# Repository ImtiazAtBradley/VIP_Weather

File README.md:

# This Repository Has Moved!!!!!

[github.com/ece398-buvip/vip-weather](https://github.com/ece398-buvip/vip-weather)

# Bradley Weather Station - Overview

The source code for the Bradley Weather Station website/api/firmware/broker. The data produced by the station is available at [weather.jacobsimeone.net](https://weather.jacobsimeone.net). 

- [Hardware Design on OnShape](https://cad.onshape.com/documents/38c15368c41f2224b0adceca/w/e0d05cb6b75a73d47582f798/e/6f88f03cdb676fd77e352c81)
- [Documentation](https://litemage.github.io/vip-weather-docs/)
- [Documentation GitHub (separate from this repository)](https://github.com/Litemage/vip-weather-docs)

# Contributors

**Spring 2024**
- Jacob S. 
- Kyle K.
- Christopher H.
- Emily A.
- Owen J.
- Samantha P.
- Dr. Imtiaz - **Advisor**

**Fall 2024**
- Ryuto N.
- Freddie M.
- Logan V.
- Grace T.

**Spring 2025**
- Matthew V.
- Riley P.

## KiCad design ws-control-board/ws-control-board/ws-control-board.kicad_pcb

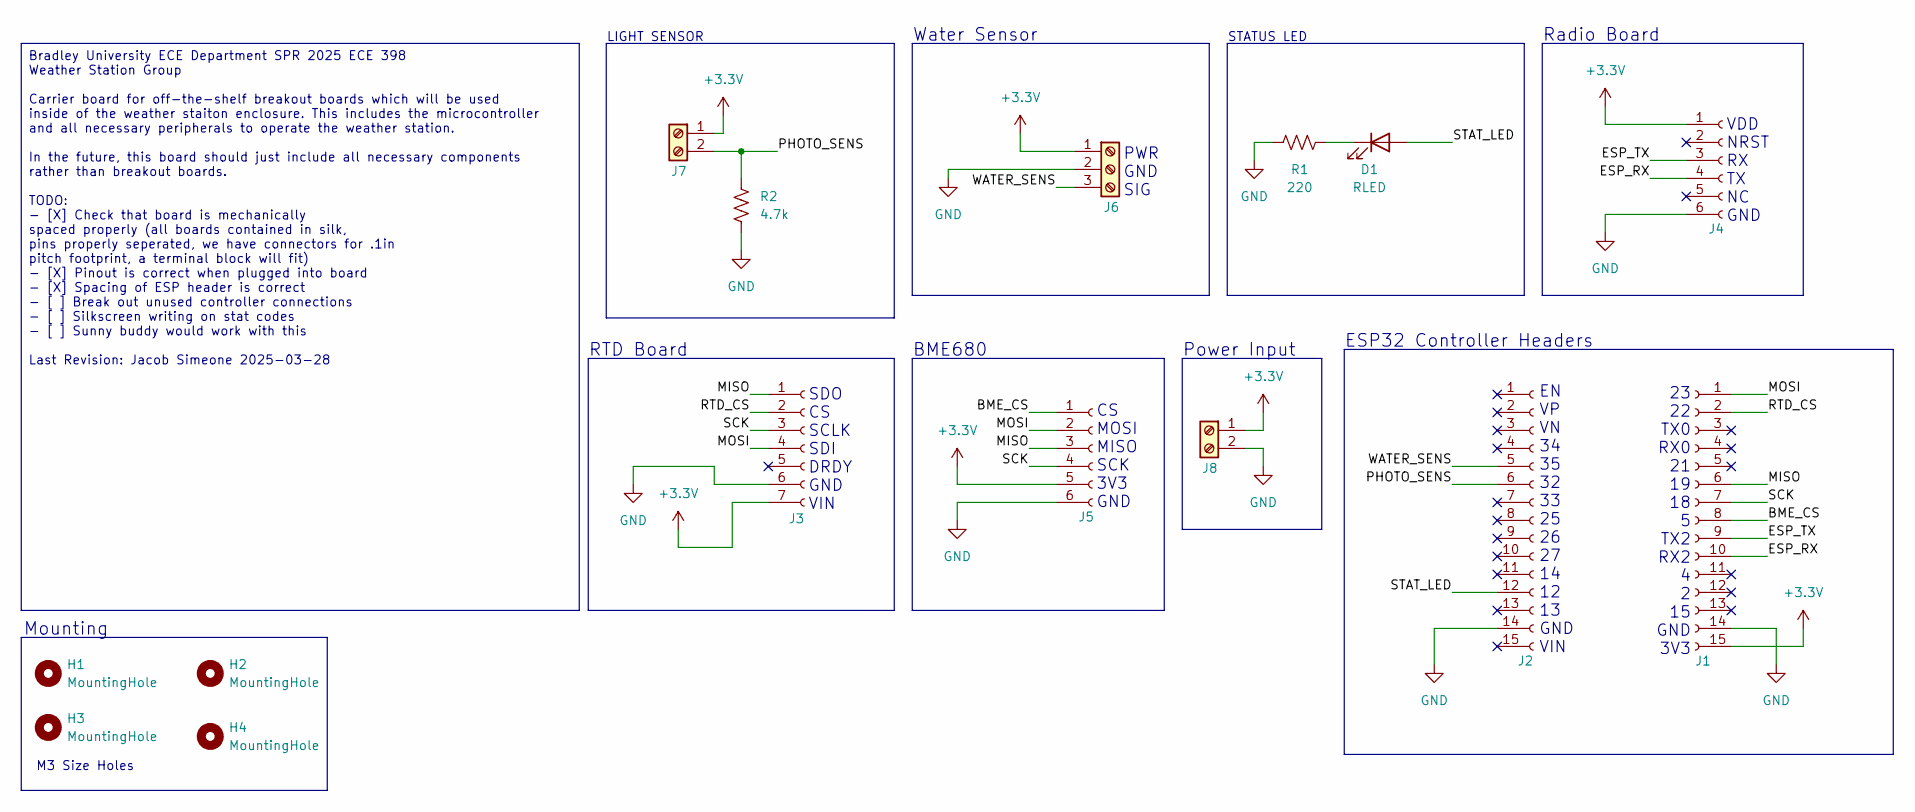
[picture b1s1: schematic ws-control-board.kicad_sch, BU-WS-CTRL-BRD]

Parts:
D1: RLED; LED_D5.0mm
H1, H2, H3, H4: MountingHole; MountingHole_3.2mm_M3
J1, J2: Conn_01x15_Socket; PinSocket_1x15_P2.54mm_Vertical
J3: Conn_01x07_Socket; PinSocket_1x07_P2.54mm_Vertical
J4, J5: Conn_01x06_Socket; PinSocket_1x06_P2.54mm_Vertical
J6: Screw_Terminal_01x03; PinHeader_1x03_P2.54mm_Vertical
J7, J8: Screw_Terminal_01x02; PinHeader_1x02_P2.54mm_Vertical
R1: 220; R_Axial_DIN0207_L6.3mm_D2.5mm_P10.16mm_Horizontal
R2: 4.7k; R_Axial_DIN0207_L6.3mm_D2.5mm_P10.16mm_Horizontal

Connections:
+3.3V: J1.15, J3.7, J4.1, J5.5, J6.1, J7.1, J8.1
/BME_CS: J1.8, J5.1
/ESP_RX: J1.10, J4.4
/ESP_TX: J1.9, J4.3
/MISO: J1.6, J3.1, J5.3
/MOSI: J1.1, J3.4, J5.2
/PHOTO_SENS: J2.6, J7.2, R2.2
/RTD_CS: J1.2, J3.2
/SCK: J1.7, J3.3, J5.4
/STAT_LED: D1.2 (A), J2.12
/WATER_SENS: J2.5, J6.3
GND: J1.14, J2.14, J3.6, J4.6, J5.6, J6.2, J8.2, R1.1, R2.1
unnamed: D1.1 (K), R1.2

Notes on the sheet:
Radio Board
CS MOSI MISO SCK 3V3 GND
PWR GND SIG
SDO CS SCLK SDI DRDY GND VIN
M3 Size Holes
RTD Board
Mounting
STATUS LED
VDD NRST RX TX NC GND
23 22 TX0 RX0 21 19 18 5 TX2 RX2 4 2 15 GND 3V3
BME680
EN VP VN 34 35 32 33 25 26 27 14 12 13 GND VIN
LIGHT SENSOR
Power Input
ESP32 Controller Headers
Water Sensor
Bradley University ECE Department SPR 2025 ECE 398 Weather Station Group Carrier board for off-the-shelf breakout boards which will be used inside of the weather staiton enclosure. This includes the microcontroller and all necessary peripherals to operate the weather station. In the future, this bo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

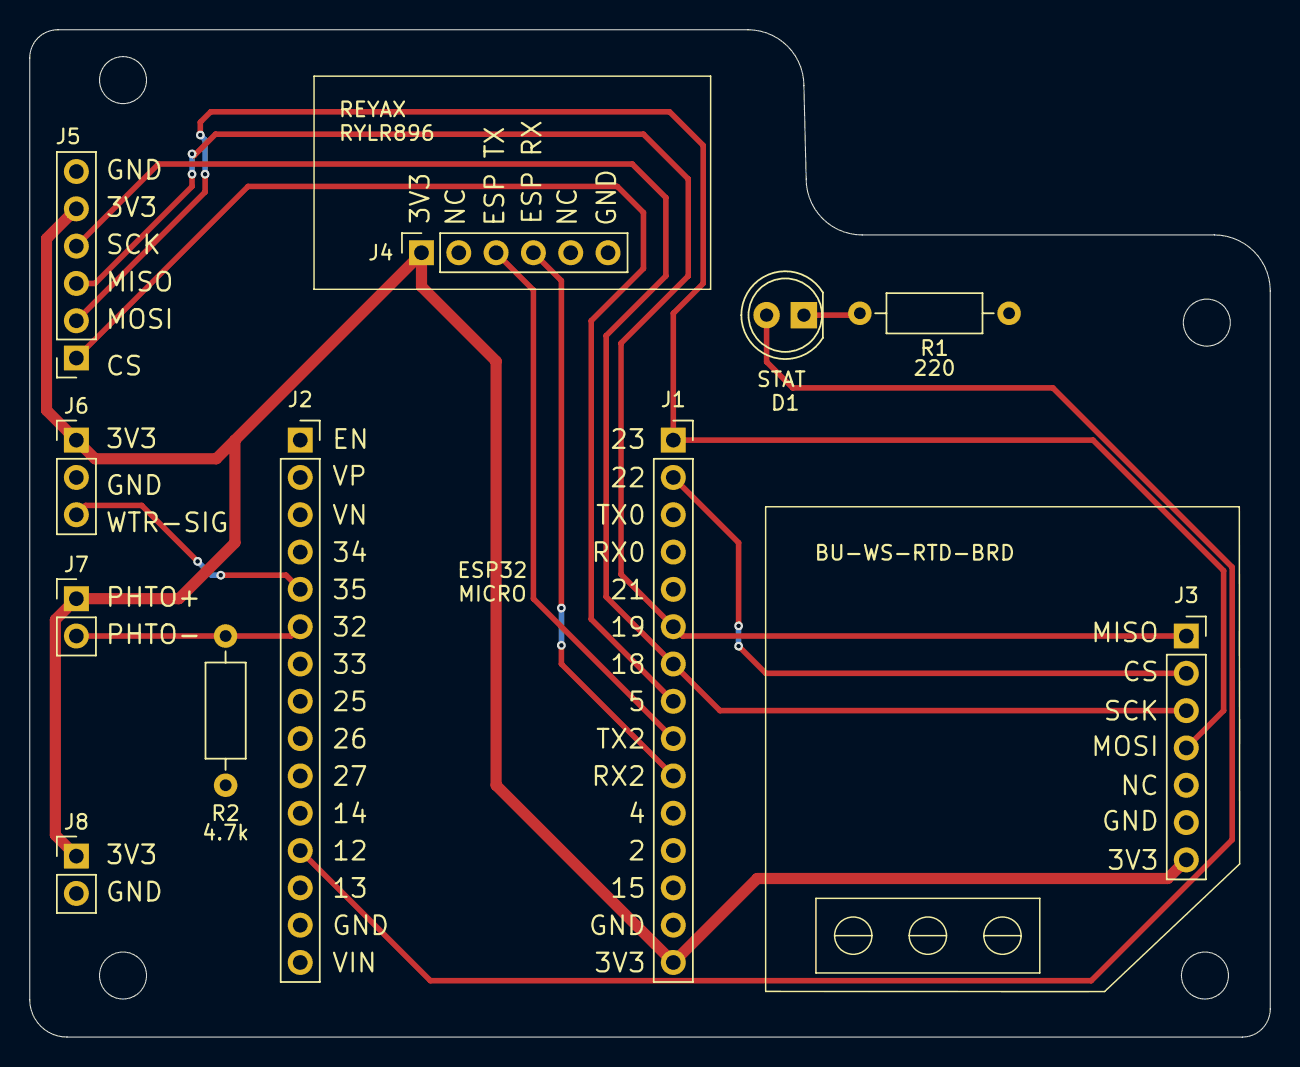
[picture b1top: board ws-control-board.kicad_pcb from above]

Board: 2 copper layers, 84.5 x 68.6 mm, 15 parts (0 on the bottom side), 13 nets.

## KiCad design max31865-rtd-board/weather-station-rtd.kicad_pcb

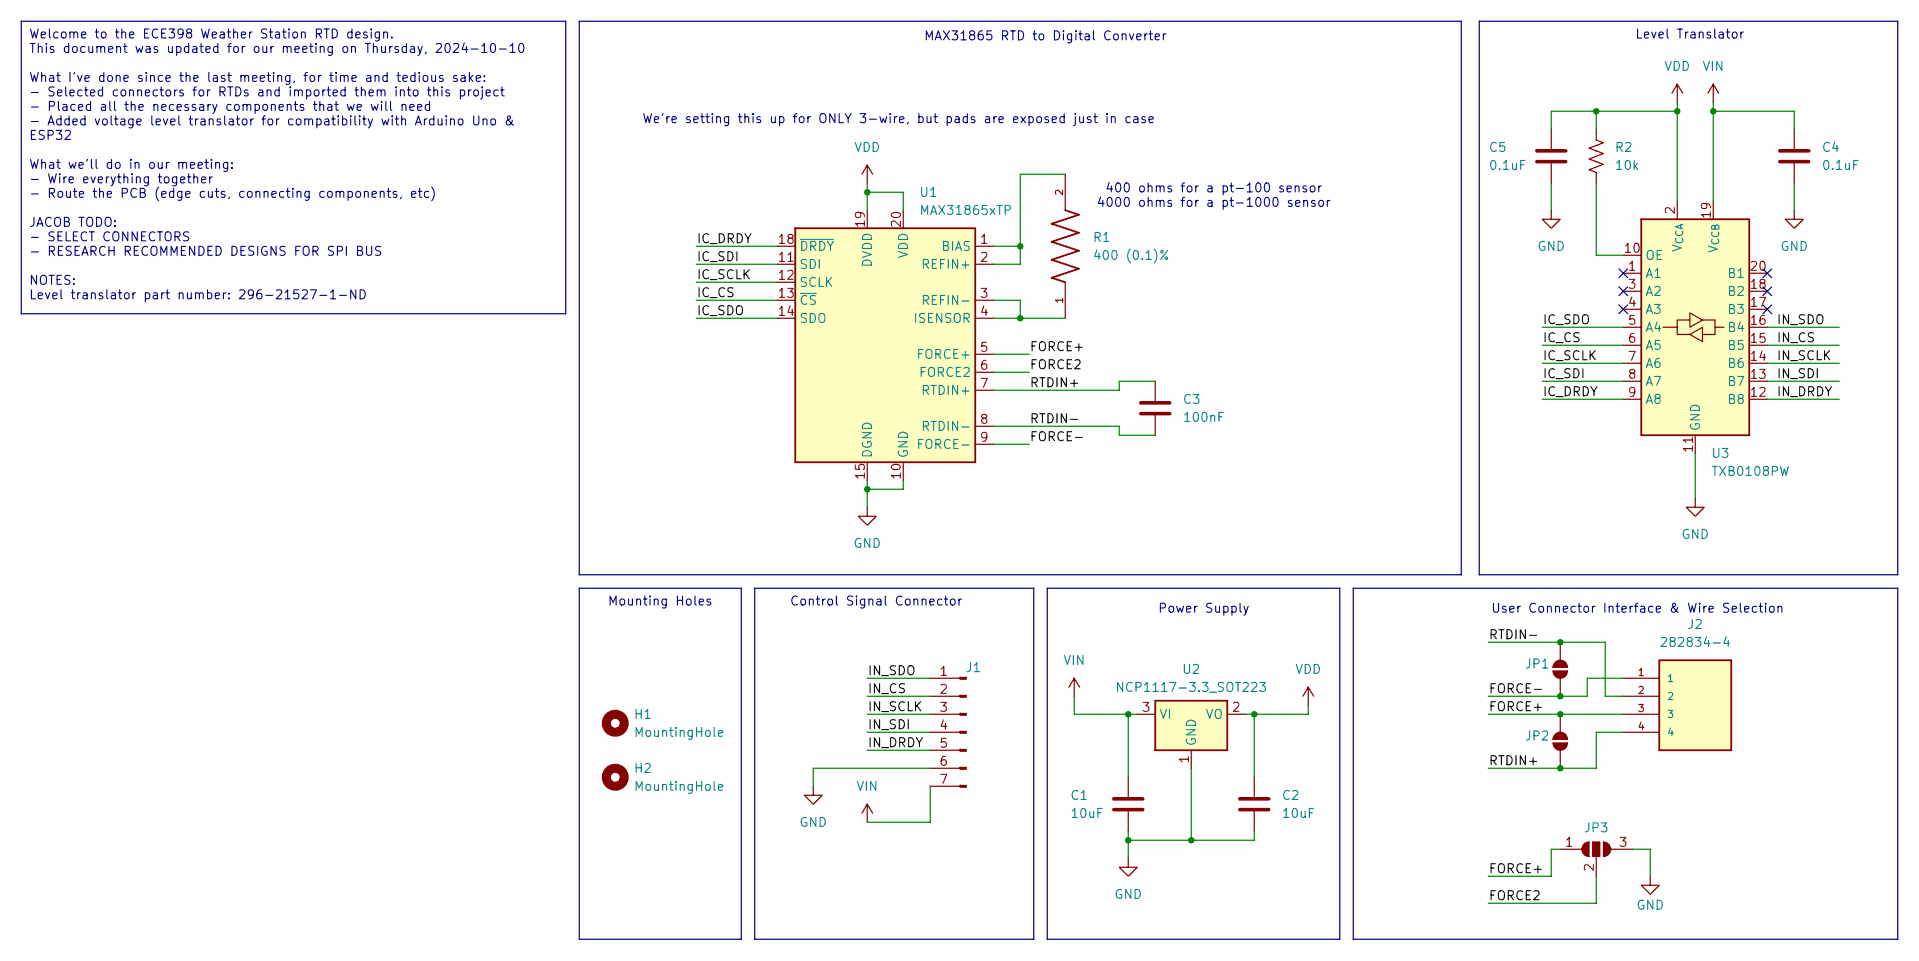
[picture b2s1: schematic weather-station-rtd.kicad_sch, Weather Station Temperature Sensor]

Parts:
C1, C2: 10uF; C_0805_2012Metric
C3: 100nF; C_0805_2012Metric
C4, C5: 0.1uF; C_0805_2012Metric
H1, H2: MountingHole; MountingHole_3.2mm_M3
J1: Conn_01x05_Pin; PinHeader_1x07_P2.54mm_Vertical
J2: 282834-4; TE_282834-4; PARTREV D
JP1, JP2: SolderJumper-2_P1.3mm_Open_TrianglePad1.0x1.5mm
JP3: SolderJumper-3_P1.3mm_Open_RoundedPad1.0x1.5mm_NumberLabels
R1: 400 (0.1)%; RESC3116X65N
R2: 10k; C_0805_2012Metric
U1: MAX31865xTP; TQFN-20-1EP_5x5mm_P0.65mm_EP3.25x3.25mm
U2: NCP1117-3.3_SOT223; SOT-223-3_TabPin2
U3: TXB0108PW; TSSOP-20_4.4x6.5mm_P0.65mm

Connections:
/FORCE2: JP3.2 (C), U1.6 (FORCE2)
/FORCE+: J2.3, JP2.2 (B), JP3.1 (A), U1.5 (FORCE+)
/FORCE-: J2.1, JP1.1 (A), U1.9 (FORCE-)
/IC_CS: U1.13 (~CS), U3.6 (A5)
/IC_DRDY: U1.18 (~DRDY), U3.9 (A8)
/IC_SCLK: U1.12 (SCLK), U3.7 (A6)
/IC_SDI: U1.11 (SDI), U3.8 (A7)
/IC_SDO: U1.14 (SDO), U3.5 (A4)
/IN_CS: J1.2, U3.15 (B5)
/IN_DRDY: J1.5, U3.12 (B8)
/IN_SCLK: J1.3, U3.14 (B6)
/IN_SDI: J1.4, U3.13 (B7)
/IN_SDO: J1.1, U3.16 (B4)
/RTDIN+: C3.1, J2.4, JP2.1 (A), U1.7 (RTDIN+)
/RTDIN-: C3.2, J2.2, JP1.2 (B), U1.8 (RTDIN-)
GND: C1.2, C2.2, C4.2, C5.2, J1.6, JP3.3 (B), U1.10 (GND), U1.15 (DGND), U1.16 (GND), U1.21 (GND), U2.1 (GND), U3.11 (GND)
unnamed: R1.2, U1.1 (BIAS), U1.2 (REFIN+)
unnamed: R1.1, U1.3 (REFIN-), U1.4 (ISENSOR)
unnamed: R2.2, U3.10 (OE)
VDD: C2.1, C5.1, R2.1, U1.19 (DVDD), U1.20 (VDD), U2.2 (VO), U3.2 (V_{CCA})
VIN: C1.1, C4.1, J1.7, U2.3 (VI), U3.19 (V_{CCB})

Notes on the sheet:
Welcome to the ECE398 Weather Station RTD design. This document was updated for our meeting on Thursday, 2024-10-10 What I've done since the last meeting, for time and tedious sake: - Selected connectors for RTDs and imported them into this project - Placed all the necessary components that we will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
400 ohms for a pt-100 sensor 4000 ohms for a pt-1000 sensor
MAX31865 RTD to Digital Converter
Power Supply
Control Signal Connector
Mounting Holes
Level Translator
We're setting this up for ONLY 3-wire, but pads are exposed just in case
User Connector Interface & Wire Selection

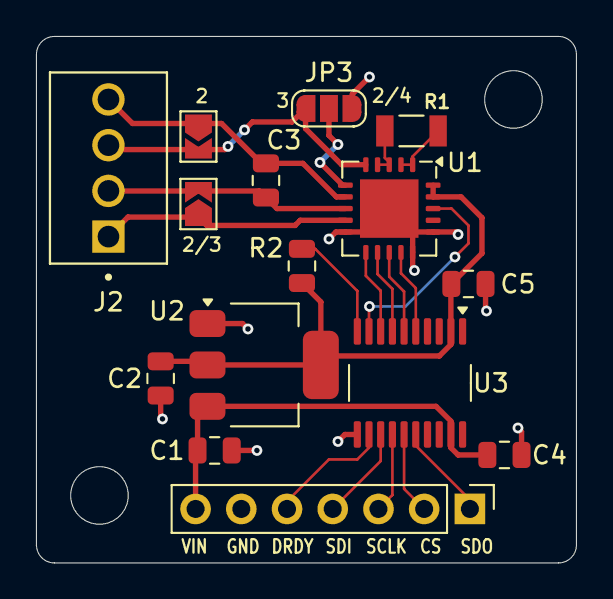
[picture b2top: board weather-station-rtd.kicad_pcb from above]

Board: 2 copper layers, 30.0 x 29.2 mm, 17 parts (0 on the bottom side), 21 nets.

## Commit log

2024-02-16 Set up platformIO project
2024-02-16 Project Template
2024-02-22 Starting point
2024-02-23 Update weather_station.cpp
    idk man, i did some stuff but whether its right... ???
2024-02-27 initial website code
2024-02-28 Working website
2024-02-28 Update README.md
    Update README with instructions
2024-02-29 Organization - Pretty Website
2024-03-01 Reorganize
2024-03-01 Remove Bootstrap - Add Information
    - Bootstrap is too big to merit use on ESP32
    - Add own styling + Information
2024-03-01 Fix Spelling
    I forgot to turn on my spell check...
2024-03-01 protype weather station
2024-03-01 Fix Bugs
    - Fix: Samantha's initial
    - Light sensor threshold
    - Weird character on page
    - Redirection on windows computers
2024-03-01 Fix table for mobile
2024-03-04 Increase Power
2024-03-07 Change to degrees F
2024-03-19 Move to BME280, Update for hardware changes
2024-03-28 Add bradley-cast protocol
2024-04-01 Protocol - Passing tests
2024-04-05 Broker compiling (linux)
2024-04-05 wip envData api
2024-04-11 Fix double free. DB connect
2024-04-12 Remove webserver
2024-04-12 talking radio, serial stuff
2024-04-13 Creating Website Base Files
    Adds a modified version of the basic NextJs tutorial.
2024-04-13 Create Website Components
    Adding in NextJs architecture.
2024-04-13 Working weather station firmware
2024-04-13 Prune unused files. Minimal Example
2024-04-13 Add responsiveness
2024-04-13 Prototype Webpage
2024-04-14 Broker opens serial port
2024-04-14 Broker parses incoming data
2024-04-15 Posts to database stream
2024-04-15 Prototype API
2024-04-15 Add timestamp
2024-04-15 Add settings
2024-04-15 db, broker, website all working
2024-04-17 Updates for server integration
2024-04-17 fix broker bugs. Website building
2024-04-18 Server QOL updates
2024-04-19 Dynamically change icon
2024-04-24 Ready for demo
    - Weather station tx interval at 30 seconds
    - LED lights up after transmission
    - Added configuration files
2024-04-25 More demo updates
    Fix: Memory leak
    Tweak: Change to 5 second tx time for firmware
    Fix: Update Next.js
2024-04-26 Final code for demo day
2024-04-26 Live Deployment
    Live deployment to bradley campus
2024-05-01 Website improvements
    Add: Contact page
    Add: About page
    Add: Footer
2024-05-02 Fix webpage layout issues
2024-05-02 Breakpoint improvements
2024-08-21 Add documentation images
2024-10-23 Move to typescript
2024-10-24 add post interface for database through API with authentication
2024-10-28 WIP broker change to API
2024-10-31 API Posting updates data
2024-10-31 CLI URL arg, unit test for file read
2024-11-08 website + api + broker improvements
    - Broker now posts data to API successfully
    - Added a "who build this?" section on the website
    - API data now has timestamp instead of sample
    - Broker checks for invalid API key file
2024-11-10 Updated website
2024-11-11 Fix time bug - add title
2024-11-13 update icon - add last updated string
2024-11-14 Update Firmware
    - Boot logic updated. Much more clear
    - Soft reset on boot fail
2024-11-14 Fix timestamp
2024-11-14 Implemented BME680
2024-12-06 Website Maintenance Log
2024-12-06 Add Maintenance Mode Documentation
2025-01-25 Revert "Merge pull request #8 from deviousgoose/dev/bem680"
    This reverts commit c0659df68e0beccd2334d530cdb0eb8e3aa03ed6, reversing
    changes made to 68203e5bd0544a41c5090b4a73ce95e302e5f272.
2025-01-25 Update With Currently Deployed Services
2025-02-11 Reapply "Merge pull request #8 from deviousgoose/dev/bem680"
    This reverts commit a11d2372f45b25cb712d9df007ce1cde29c17d88.
2025-02-12 Add rtd board to git
2025-02-25 Radio debugging, Data Changes
    - Change to sending analog data values for light and water
    - Remove radio reset pin
2025-03-02 Prototype Broker Code
2025-03-02 Update API
2025-03-02 Data handling changes
2025-03-02 Fix weather card
2025-03-13 Update graphs
2025-03-13 More chart changes
2025-03-13 Switch to measuring temp with RTD.
    MUST VERIFY AND INPUT CS PIN
2025-03-27 General UI Improvements
2025-03-27 Spelling Fixes
    U suck at spelling
2025-03-29 Add a control board to mount inside the station
2025-03-30 Update Firmware
2025-03-30 Fix board bugs
2025-04-03 General Fixes
    Just made some general fixes
2025-04-04 Update schematic todo
2025-04-09 Add data sim and change charts back to lines
2025-04-09 Add issues reference. Update Year
2025-04-09 Show NWS Data When in Maintenance Mode
2025-04-24 Add sbdlog to project WIP
2025-04-24 Update README.md
    Added Spring 2025
2025-04-24 Pre-Flight Fixes
2025-05-03 Only display last 48 hrs. Alert for bad data
2025-05-08 Fixed compile errors. Added spdlog to cmake
2025-05-08 Move logging over to wslogger
2025-05-08 Format code. Add sanity check
2025-06-18 Update Website
    - Fix alert
    - Fix crash
    - Add News
    - Add rain icon on raining
